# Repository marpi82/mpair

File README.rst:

======
mpair
======

Advanced Air Quality Monitoring Station
========================================

**mpair** is an open-source IoT air quality monitoring station with support for Matter/Thread protocol, PoE+ connectivity, and professional-grade sensors.

.. image:: https://img.shields.io/badge/Hardware-CERN--OHL--S--2.0-blue
   :target: LICENSE-hardware.rst
   :alt: Hardware License

.. image:: https://img.shields.io/badge/Software-GPL--3.0-green
   :target: LICENSE-software.rst
   :alt: Software License

.. image:: https://img.shields.io/badge/Documentation-CC--BY--SA--4.0-orange
   :target: LICENSE-docs.rst
   :alt: Documentation License

Features
========

Hardware Features
-----------------

* **Single MCU Architecture**

  * ESP32-C6-WROOM-1-N8 (all-in-one controller with integrated 802.15.4 radio)

* **Connectivity**

  * Matter over Thread support (native 802.15.4 radio)
  * WiFi 6 (802.11ax) 2.4GHz
  * Ethernet 10/100Mbps via W5500 (SPI)
  * PoE/PoE+ (802.3af/at) with RT5300B-12V or 12V DC jack
  * CP2102 USB-UART converter for programming

* **Sensors**

  * SPS30 - Particulate Matter sensor (PM1.0, PM2.5, PM4.0, PM10)
  * MH-Z14A - NDIR CO₂ sensor
  * SHT31 - Temperature and humidity (indoor)
  * BME280 - Temperature, humidity, and barometric pressure (outdoor)
  * GPS NEO-6 - Location and time synchronization

* **Additional Features**

  * PTC heater (70°C) for HECA - heats air to reduce relative humidity and prevent SPS30 from measuring water droplets
  * WS2812 RGB LED indicators
  * SSD1309 2.42" OLED display (128×64, optional for indoor version)

Software Features
-----------------

* Matter/Thread protocol support for smart home integration
* Real-time air quality monitoring
* Data logging and visualization
* OTA firmware updates
* Web-based configuration interface
* Multiple data export protocols:

  * MQTT broker support
  * Prometheus metrics endpoint
  * JSON REST API endpoint
  * Data publishing to Luftdaten (sensor.community)
  * Data publishing to madavi.de
  * Data publishing to opensensemap.org
  * Data publishing to aqi.eco

Technical Specifications
========================

Power Supply
------------

* **Input:** PoE/PoE+ (802.3af/at) or 12V DC jack
* **Power Rails:** 12V, 5V, 3.3V (isolated Buck converters with TX4138)
* **Consumption:** TBD

Communication Interfaces
------------------------

* **Ethernet:** 10/100Mbps via W5500 (SPI)
* **Wireless:** WiFi 6 (802.11ax) 2.4GHz, Matter over Thread (native 802.15.4 radio)
* **USB-UART:** CP2102 converter for programming and debugging

Measurement Ranges
------------------

* **PM:** 0-1000 µg/m³ (PM1.0, PM2.5, PM4.0, PM10)
* **CO₂:** 0-5000 ppm (MH-Z14A)
* **Temperature:** -40°C to +85°C
* **Humidity:** 0-100% RH
* **Pressure:** 300-1100 hPa (BME280)

Project Structure
=================

::

    mpair/
    ├── hardware/
    │   ├── EasyEDA/           # EasyEDA Pro project files
    │   ├── gerbers/           # Manufacturing files (Gerber, drill, BOM)
    │   └── schematics/        # PDF schematics and documentation
    ├── software/
    │   ├── firmware/          # ESP32 firmware (ESP-IDF / Arduino)
    │   ├── bootloader/        # Custom bootloader (if needed)
    │   └── tests/             # Unit and integration tests
    └── docs/                  # Additional documentation

Getting Started
===============

Prerequisites
-------------

* Thread Border Router (e.g., Smilight SLZB-06M) for Matter/Thread connectivity
* Smart home system with Matter support (Home Assistant, Apple Home, Google Home, etc.) - optional
* ESP-IDF v5.x or Arduino-ESP32 v3.x
* EasyEDA Pro (for hardware modifications)

Building Firmware
-----------------

.. code-block:: bash

    cd software/firmware
    idf.py build
    idf.py flash monitor

Hardware Assembly
-----------------

Detailed assembly instructions and BOM are available in the ``hardware/`` directory.

Configuration
-------------

1. Connect the device via USB, Ethernet, or power it with PoE/DC
2. Access the web interface at ``http://mpair.local``
3. Configure Thread credentials, sensor parameters, and data publishing settings
4. (Optional) Pair with your smart home system using Matter QR code
5. Configure data export endpoints (MQTT, Prometheus, Luftdaten, etc.)

Licenses
========

This project uses multiple licenses for different components:

Hardware
--------

**CERN Open Hardware Licence Version 2 - Strongly Reciprocal (CERN-OHL-S-2.0)**

The hardware designs are licensed under CERN-OHL-S-2.0, which means:

* You are free to use, modify, and distribute the hardware designs
* Any modifications must be released under the same license
* You must make design sources available
* Commercial use is allowed

See `LICENSE-hardware.rst <LICENSE-hardware.rst>`_ for full license text.

Software
--------

**GNU General Public License v3.0 (GPL-3.0)**

The software (firmware, utilities) is licensed under GPL-3.0, which means:

* You are free to use, modify, and distribute the software
* Any modifications must be released under the same license
* Source code must be made available
* Commercial use is allowed

See `LICENSE-software.rst <LICENSE-software.rst>`_ for full license text.

Documentation
-------------

**Creative Commons Attribution-ShareAlike 4.0 International (CC BY-SA 4.0)**

All documentation is licensed under CC BY-SA 4.0, which means:

* You are free to share and adapt the documentation
* You must give appropriate credit
* You must distribute your contributions under the same license
* Commercial use is allowed

See `LICENSE-docs.rst <LICENSE-docs.rst>`_ for full license text.

Contributing
============

Contributions are welcome! Please:

1. Fork the repository
2. Create a feature branch (``git checkout -b feature/amazing-feature``)
3. Commit your changes (``git commit -m 'Add amazing feature'``)
4. Push to the branch (``git push origin feature/amazing-feature``)
5. Open a Pull Request

Please ensure your contributions comply with the respective licenses.

Credits
=======

* Inspired by NAMF (Nettigo Air Monitor Firmware)
* Hardware design references from Olimex ESP32-PoE2
* Matter/Thread support via ESP-IDF

Support
=======

* **Issues:** Use GitHub Issues for bug reports and feature requests
* **Discussions:** Use GitHub Discussions for questions and ideas
* **Documentation:** Check the `docs/ <docs/>`_ directory for detailed information

Roadmap
=======

* ☐ PCB design and prototyping
* ☐ Firmware development (ESP32-C6)
* ☐ Matter device type implementation
* ☐ Home Assistant integration and testing
* ☐ Enclosure design (3D printable)
* ☐ Certification (optional - Matter, PoE)
* ☐ Production-ready version

Disclaimer
==========

This project is provided "as-is" without any warranty. The authors are not responsible for any damage or data loss resulting from the use of this hardware or software.

----

**Made with ❤️ for clean air monitoring**

*Version: 0.1.0-alpha*

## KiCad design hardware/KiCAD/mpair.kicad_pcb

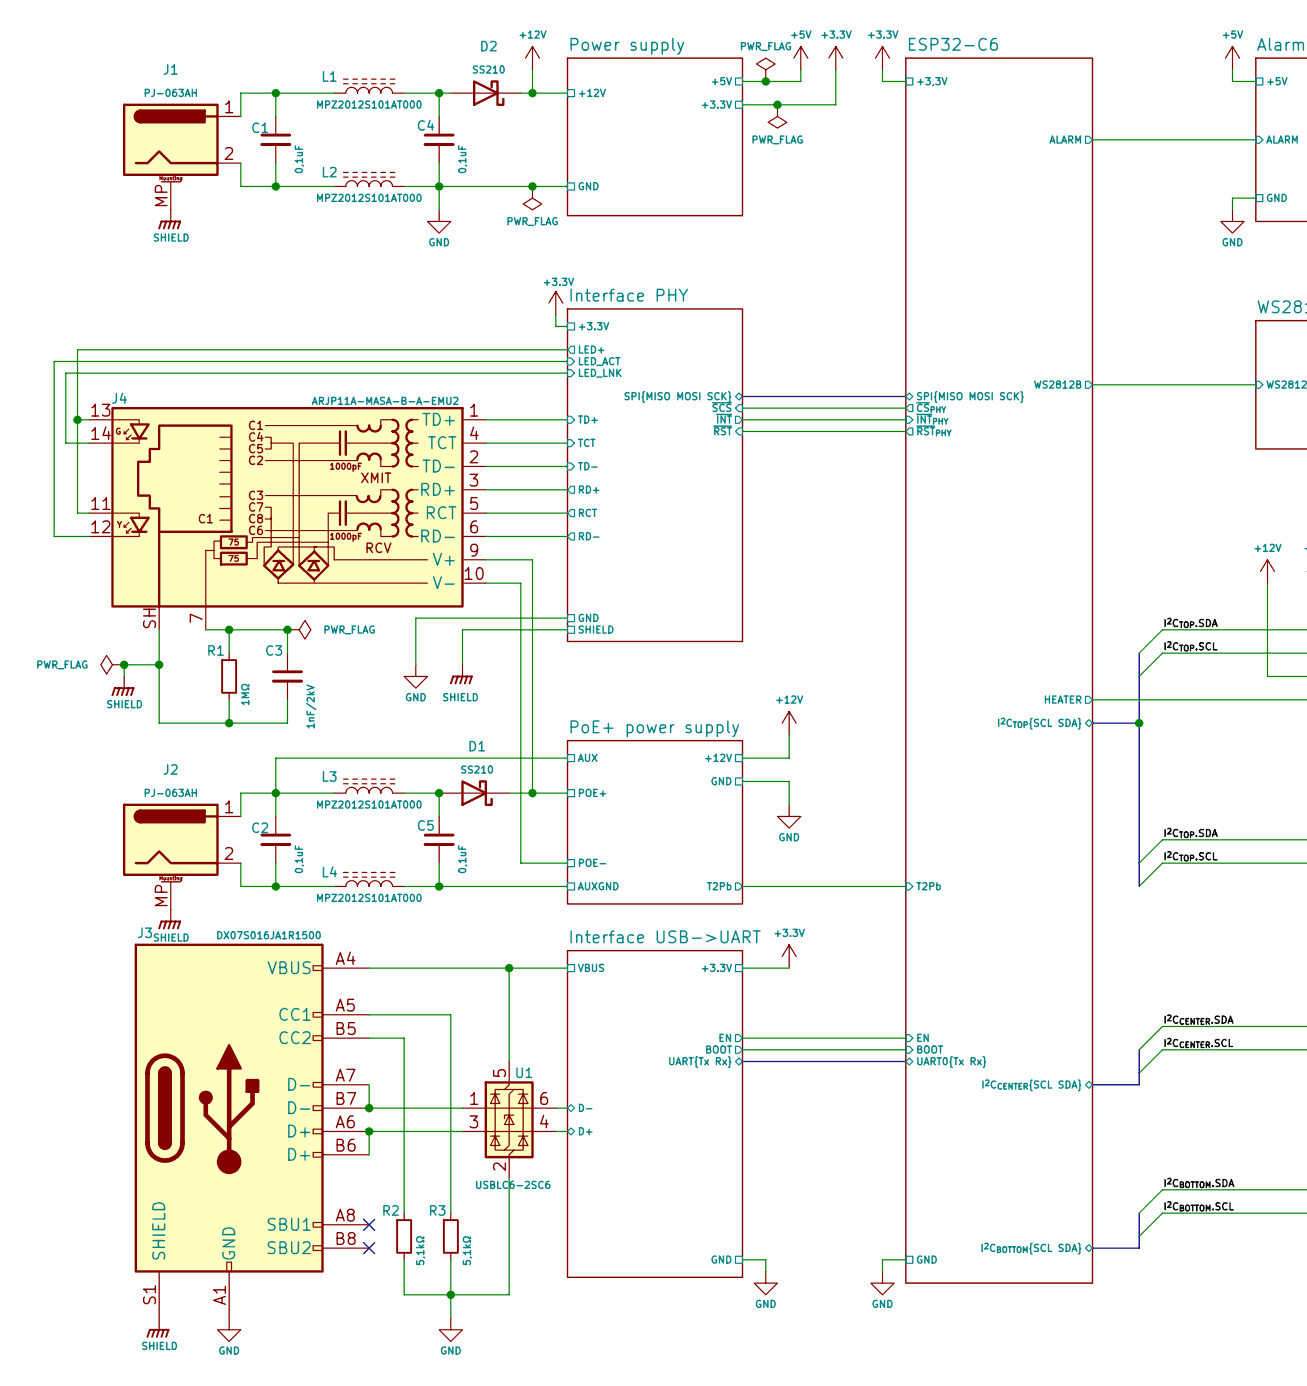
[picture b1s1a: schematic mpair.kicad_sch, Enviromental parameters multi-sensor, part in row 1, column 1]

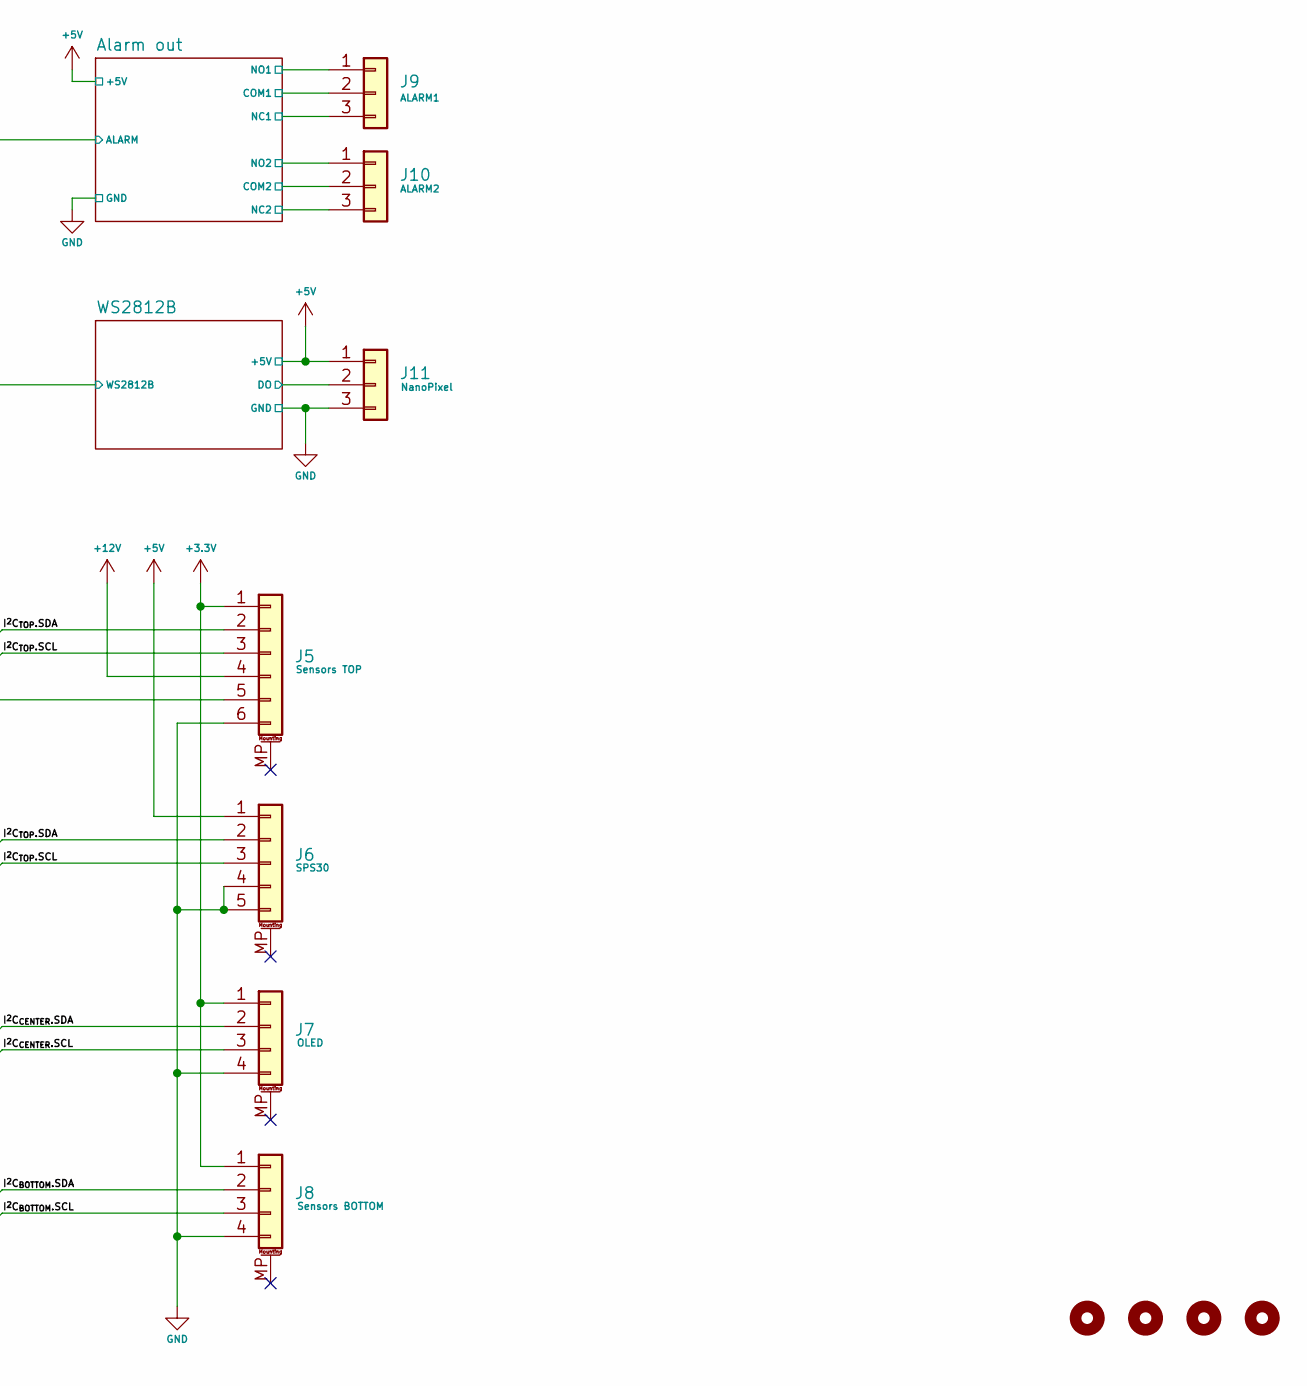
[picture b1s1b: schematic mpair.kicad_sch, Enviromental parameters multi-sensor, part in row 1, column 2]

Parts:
C1, C2, C4, C5: 0,1uF; C_0603_1608Metric; Manufacturer_Part_Number Samsung; DigiKey_Part_Number 1276-1018-1-ND
C3: 1nF/2kV; C_1812_4532Metric; Manufacturer_Part_Number Kemet; DigiKey_Part_Number 399-C1812C102KGRACTUCT-ND
D1, D2: SS210; D_SMA; Manufacturer_Part_Number Comchip Technology; DigiKey_Part_Number 641-SS210-HFCT-ND
H1, H2, H3, H4: MountingHole; MountingHole_2.7mm_M2.5
J1, J2: PJ-063AH; BarrelJack_CUI_PJ-063AH_Horizontal; Manufacturer_Part_Number Same Sky (Formerly CUI Devices); DigiKey_Part_Number CP-063AH-ND
J3: DX07S016JA1R1500; USB_C_Receptacle_JAE_DX07S016JA1R1500; Manufacturer_Part_Number JAE Electronics; DigiKey_Part_Number 670-DX07S016JA1R1500CT-ND
J4: ARJP11A-MASA-B-A-EMU2; RJ45_Abracon_ARJP11A-MA_Horizontal; Manufacturer_Part_Number Abracon LLC; DigiKey_Part_Number ARJP11A-MASA-B-A-EMU2-ND
J5: JST_ZH_B6B-ZR-SM4-TF_1x06-1MP_P1.50mm_Vertical; Manufacturer_Part_Number JST Sales America Inc.; DigiKey_Part_Number 455-B6B-ZR-SM4-TFCT-ND
J6: JST_ZH_B5B-ZR-SM4-TF_1x05-1MP_P1.50mm_Vertical; Manufacturer_Part_Number JST Sales America Inc.; DigiKey_Part_Number 455-1684-1-ND
J7, J8: JST_ZH_B4B-ZR-SM4-TF_1x04-1MP_P1.50mm_Vertical; Manufacturer_Part_Number JST Sales America Inc.; DigiKey_Part_Number 455-B4B-ZR-SM4-TFCT-ND
J9, J10, J11: Molex_KK-254_AE-6410-03A_1x03_P2.54mm_Vertical; Manufacturer_Part_Number Molex; DigiKey_Part_Number WM4112-ND
L1, L2, L3, L4: MPZ2012S101AT000; L_0805_2012Metric; Manufacturer_Part_Number TDK Corporation; DigiKey_Part_Number 445-MPZ2012S101AT000CT-ND
R1: 1MΩ; R_0603_1608Metric; Tolerance 1%; Manufacturer_Part_Number Vishay Dale; DigiKey_Part_Number 541-1.00MHCT-ND
R2, R3: 5,1kΩ; R_0603_1608Metric; Tolerance 1%; Manufacturer_Part_Number Vishay Dale; DigiKey_Part_Number 541-5.10KHCT-ND
U1: USBLC6-2SC6; SOT-23-6; Manufacturer_Part_Number Shenzhen Slkormicro Semicon Co., Ltd.; DigiKey_Part_Number 5399-USBLC6-2SC6CT-ND

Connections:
+3.3V: J5.1, J7.1, J8.1; also elsewhere on the board
+5V: J6.1, J11.1; also elsewhere on the board
+12V: D2.1 (K), J5.4; also elsewhere on the board
/Alarm out/COM1: J9.2; also elsewhere on the board
/Alarm out/COM2: J10.2; also elsewhere on the board
/Alarm out/NC1: J9.3; also elsewhere on the board
/Alarm out/NC2: J10.3; also elsewhere on the board
/Alarm out/NO1: J9.1; also elsewhere on the board
/Alarm out/NO2: J10.1; also elsewhere on the board
/ESP32-C6/HEATER: J5.5; also elsewhere on the board
/ESP32-C6/I^{2}C_{BOTTOM}.SCL: J8.3; also elsewhere on the board
/ESP32-C6/I^{2}C_{BOTTOM}.SDA: J8.2; also elsewhere on the board
/ESP32-C6/I^{2}C_{CENTER}.SCL: J7.3; also elsewhere on the board
/ESP32-C6/I^{2}C_{CENTER}.SDA: J7.2; also elsewhere on the board
/ESP32-C6/I^{2}C_{TOP}.SCL: J5.3, J6.3; also elsewhere on the board
/ESP32-C6/I^{2}C_{TOP}.SDA: J5.2, J6.2; also elsewhere on the board
/Interface PHY/LED+: J4.11, J4.13; also elsewhere on the board
/Interface PHY/LED_ACT: J4.12; also elsewhere on the board
/Interface PHY/LED_LNK: J4.14; also elsewhere on the board
/Interface PHY/RCT: J4.5 (RCT); also elsewhere on the board
/Interface PHY/RD+: J4.3 (RD+); also elsewhere on the board
/Interface PHY/RD-: J4.6 (RD-); also elsewhere on the board
/Interface PHY/TCT: J4.4 (TCT); also elsewhere on the board
/Interface PHY/TD+: J4.1 (TD+); also elsewhere on the board
/Interface PHY/TD-: J4.2 (TD-); also elsewhere on the board
/Interface USB->UART/D+: U1.4 (I/O2); also elsewhere on the board
/Interface USB->UART/D-: U1.6 (I/O1); also elsewhere on the board
/Interface USB->UART/VBUS: J3.A4 (VBUS), J3.A9 (VBUS), J3.B4 (VBUS), J3.B9 (VBUS), U1.5 (VBUS); also elsewhere on the board
/PoE+ power supply/AUX: C2.1, J2.1, L3.1; also elsewhere on the board
/PoE+ power supply/AUXGND: C5.2, J4.10 (V-), L4.2; also elsewhere on the board
/PoE+ power supply/POE+: D1.1 (K), J4.9 (V+); also elsewhere on the board
/WS2812B/DO: J11.2; also elsewhere on the board
GND: C4.2, J3.A1 (GND), J3.A12 (GND), J3.B1 (GND), J3.B12 (GND), J5.6, J6.4, J6.5, J7.4, J8.4, J11.3, L2.2, R2.2, R3.2, U1.2 (GND); also elsewhere on the board
unnamed: C1.1, J1.1, L1.1
unnamed: C1.2, J1.2, L2.1
unnamed: C2.2, J2.2, L4.1
unnamed: C3.1, J4.7, R1.1
unnamed: C5.1, D1.2 (A), L3.2
unnamed: C4.1, D2.2 (A), L1.2
unnamed: J3.A5 (CC1), R3.1
unnamed: J3.B5 (CC2), R2.1
unnamed: J3.A6 (D+), J3.B6 (D+), U1.3 (I/O2)
unnamed: J3.A7 (D-), J3.B7 (D-), U1.1 (I/O1)
SHIELD: C3.2, J1.MP (MountPin), J2.MP (MountPin), J3.S1 (SHIELD), J4.SH, R1.2; also elsewhere on the board

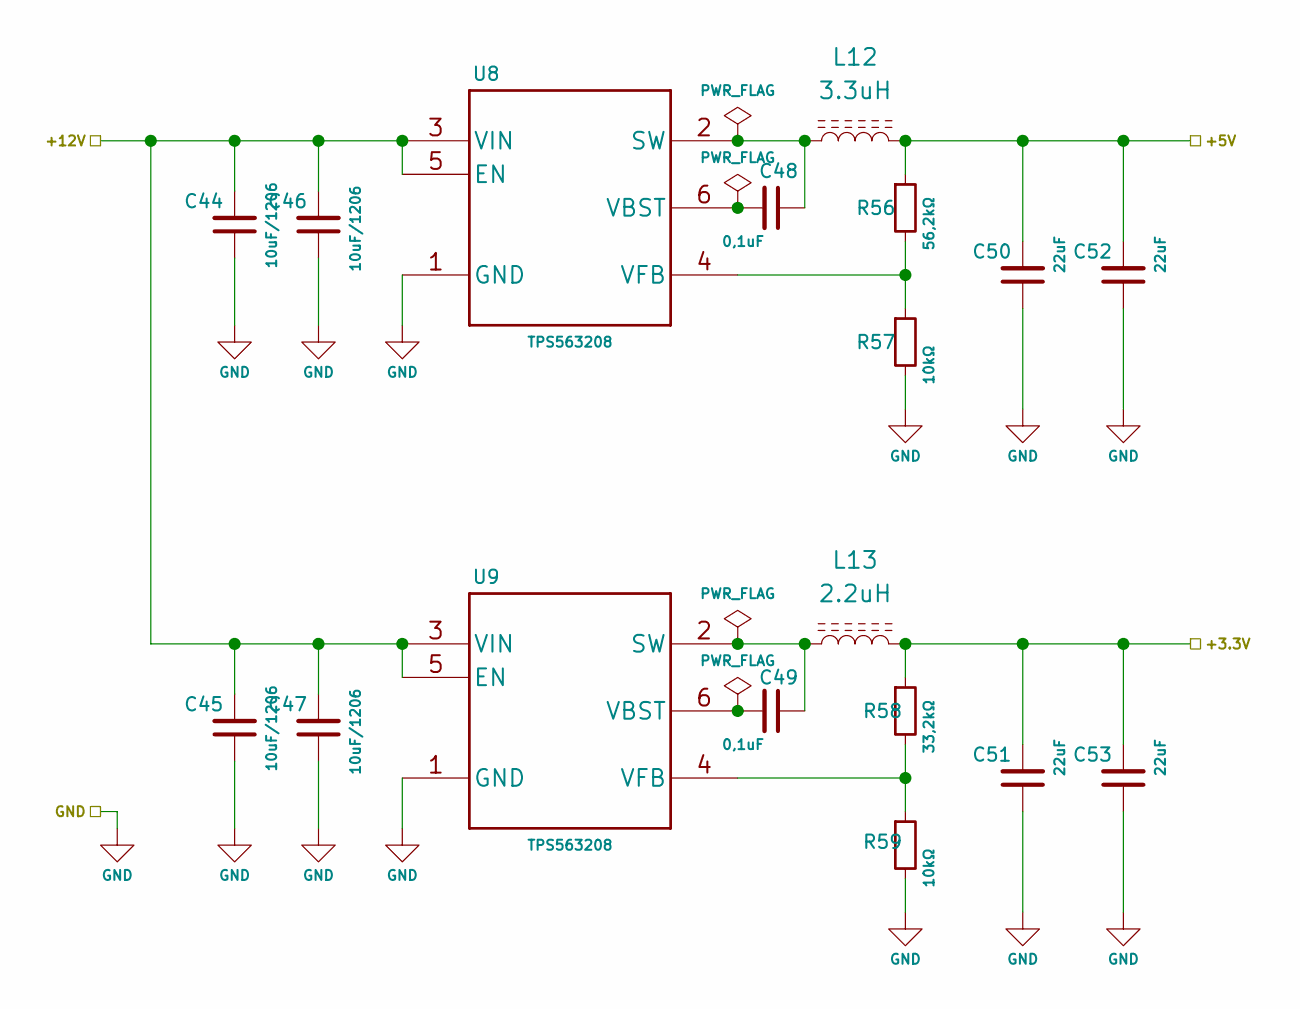
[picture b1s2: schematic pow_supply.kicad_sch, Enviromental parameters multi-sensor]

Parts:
C44, C45, C46, C47: 10uF/1206; C_1210_3225Metric; Manufacturer_Part_Number TDK; DigiKey_Part_Number 445-3942-1-ND
C48, C49: 0,1uF; C_0603_1608Metric; Manufacturer_Part_Number Samsung; DigiKey_Part_Number 1276-1018-1-ND
C50, C51, C52, C53: 22uF; C_1210_3225Metric; Manufacturer_Part_Number Samsung; DigiKey_Part_Number 1276-3392-1-ND
L12: 3.3uH; DR74; Manufacturer_Part_Number Eaton - Electronics Division; DigiKey_Part_Number 513-1665-1-ND
L13: 2.2uH; DR74; Manufacturer_Part_Number Eaton - Electronics Division; DigiKey_Part_Number 513-1140-1-ND
R56: 56,2kΩ; R_0603_1608Metric; Tolerance 1%; Manufacturer_Part_Number Vishay Dale; DigiKey_Part_Number 541-56.2KHCT-ND
R57, R59: 10kΩ; R_0603_1608Metric; Tolerance 1%; Manufacturer_Part_Number Vishay Dale; DigiKey_Part_Number 541-10.0KHCT-ND
R58: 33,2kΩ; R_0603_1608Metric; Tolerance 1%; Manufacturer_Part_Number Vishay Dale; DigiKey_Part_Number 541-33.2KHCT-ND
U8, U9: TPS563208; SOT-23-6; Manufacturer_Part_Number Texas Instruments; DigiKey_Part_Number 296-44844-1-ND

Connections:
+3.3V: C51.2, C53.2, L13.2, R58.1; also elsewhere on the board
+5V: C50.2, C52.2, L12.2, R56.1; also elsewhere on the board
+12V: C44.2, C45.2, C46.2, C47.2, U8.3 (VIN), U8.5 (EN), U9.3 (VIN), U9.5 (EN); also elsewhere on the board
GND: C44.1, C45.1, C46.1, C47.1, C50.1, C51.1, C52.1, C53.1, R57.2, R59.2, U8.1 (GND), U9.1 (GND); also elsewhere on the board
unnamed: C48.1, L12.1, U8.2 (SW)
unnamed: C48.2, U8.6 (VBST)
unnamed: R56.2, R57.1, U8.4 (VFB)
unnamed: C49.1, L13.1, U9.2 (SW)
unnamed: C49.2, U9.6 (VBST)
unnamed: R58.2, R59.1, U9.4 (VFB)

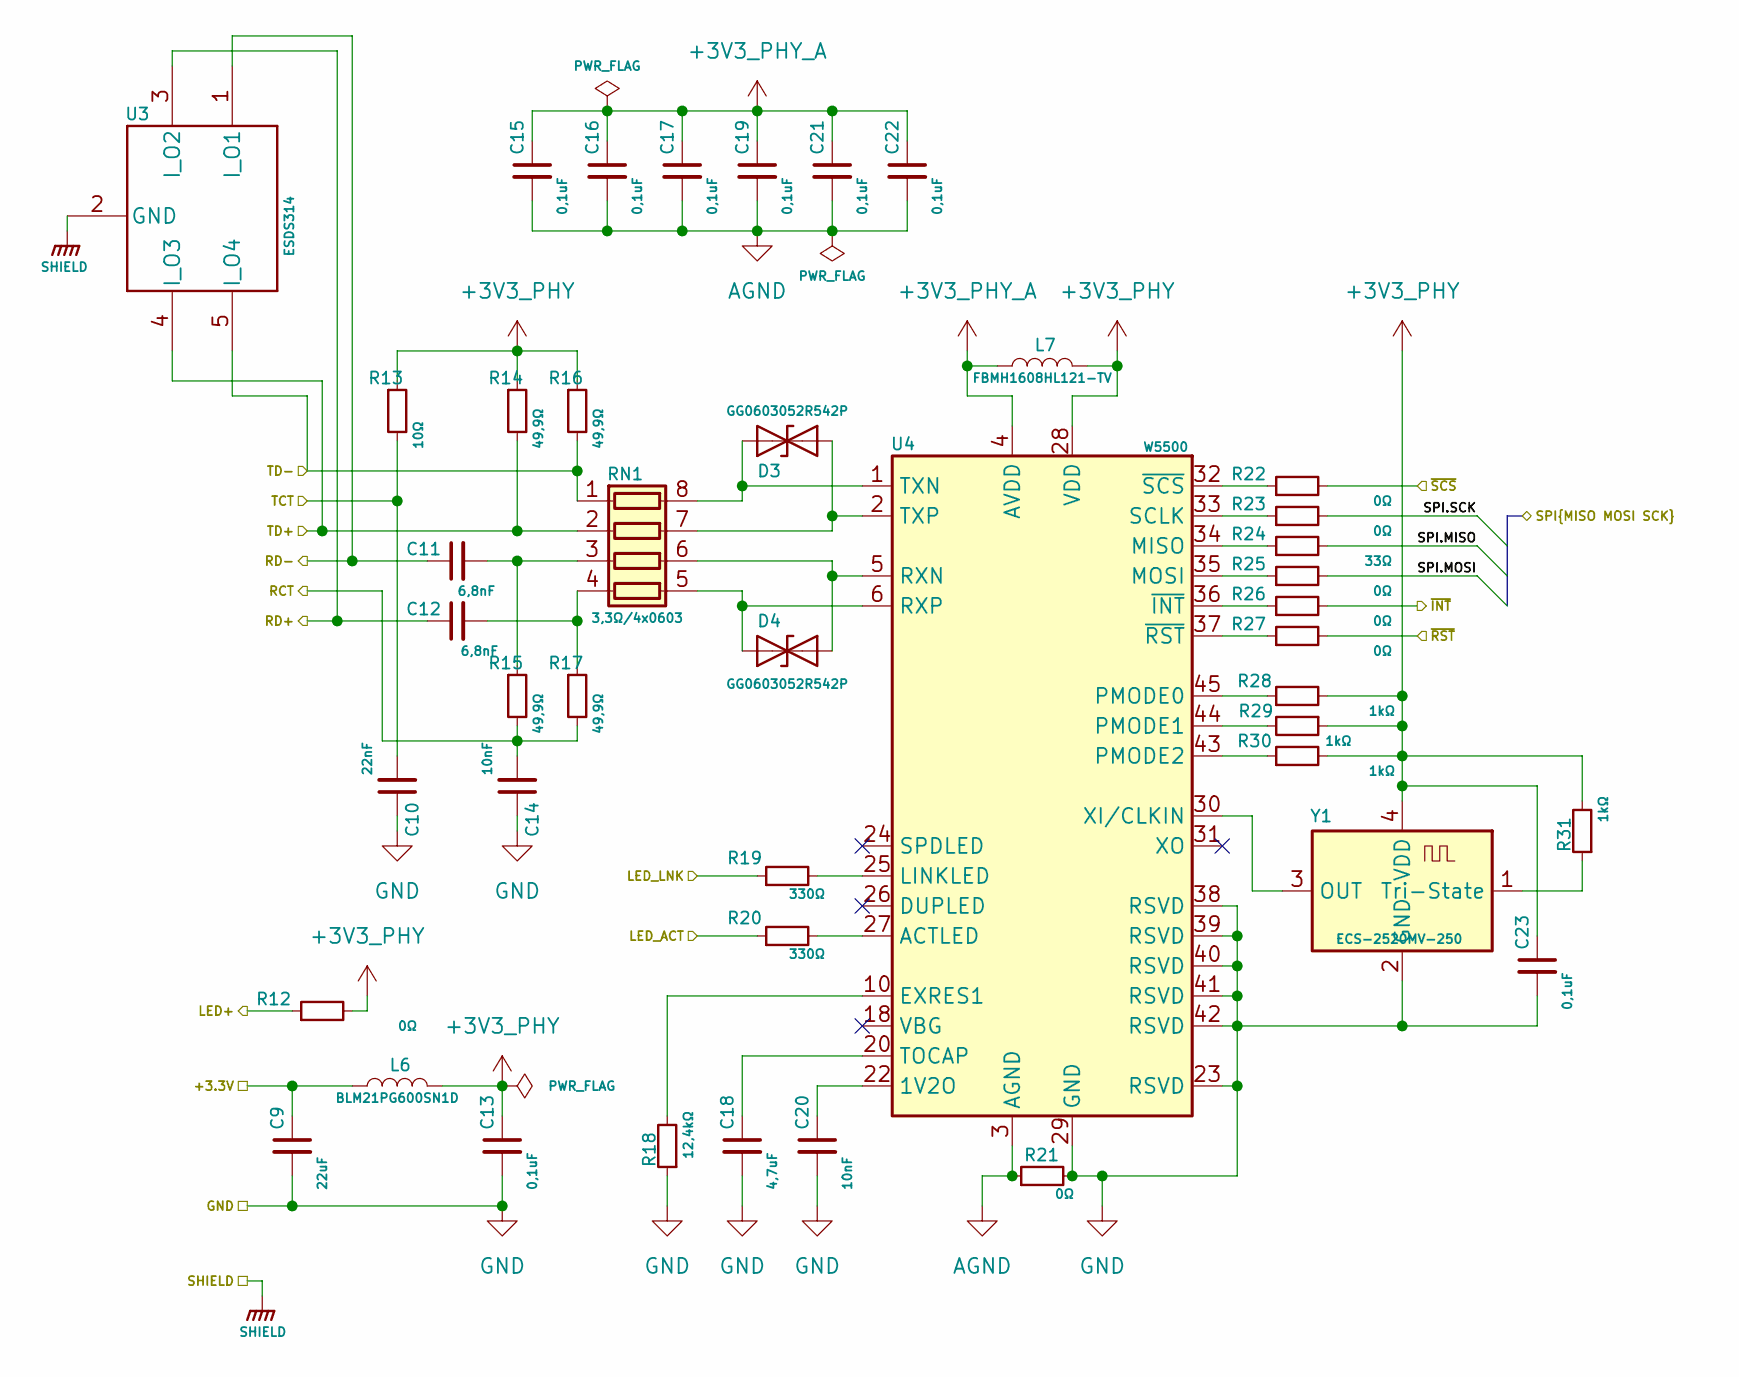
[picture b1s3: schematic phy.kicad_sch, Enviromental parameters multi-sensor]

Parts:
C9: 22uF; C_1210_3225Metric; Manufacturer_Part_Number Samsung; DigiKey_Part_Number 1276-3392-1-ND
C10: 22nF; C_0603_1608Metric; Manufacturer_Part_Number Murata; DigiKey_Part_Number 490-4782-1-ND
C11, C12: 6,8nF; C_0603_1608Metric; Manufacturer_Part_Number Kyocera; DigiKey_Part_Number 478-KAM15AR72A682KTCT-ND
C13, C15, C16, C17, C19, C21, C22, C23: 0,1uF; C_0603_1608Metric; Manufacturer_Part_Number Samsung; DigiKey_Part_Number 1276-1018-1-ND
C14, C20: 10nF; C_0603_1608Metric; Manufacturer_Part_Number Samsung; DigiKey_Part_Number 1276-1009-1-ND
C18: 4,7uF; C_0805_2012Metric; Manufacturer_Part_Number Samsung; DigiKey_Part_Number 1276-2970-1-ND
D3, D4: GG0603052R542P; D_0603_1608Metric; Manufacturer_Part_Number Kyocera; DigiKey_Part_Number 478-GG0603052R542PCT-ND
L6: BLM21PG600SN1D; L_0805_2012Metric; Manufacturer_Part_Number Murata Electronics; DigiKey_Part_Number 490-1053-1-ND
L7: FBMH1608HL121-TV; L_0603_1608Metric; Manufacturer_Part_Number Taiyo Yuden; DigiKey_Part_Number 587-3812-1-ND
R12, R21, R22, R23, R25, R26, R27: 0Ω; R_0603_1608Metric; Tolerance 1%; Manufacturer_Part_Number Vishay Dale; DigiKey_Part_Number 541-0.0GCT-ND
R13: 10Ω; R_0603_1608Metric; Tolerance 1%; Manufacturer_Part_Number Vishay Dale; DigiKey_Part_Number 541-10.0HCT-ND
R14, R15, R16, R17: 49,9Ω; R_0603_1608Metric; Tolerance 1%; Manufacturer_Part_Number Vishay Dale; DigiKey_Part_Number 541-49.9HCT-ND
R18: 12,4kΩ; R_0603_1608Metric; Tolerance 1%; Manufacturer_Part_Number Vishay Dale; DigiKey_Part_Number 541-12.4KHCT-ND
R19, R20: 330Ω; R_0603_1608Metric; Tolerance 1%; Manufacturer_Part_Number Vishay Dale; DigiKey_Part_Number 541-330HCT-ND
R24: 33Ω; R_0603_1608Metric; Tolerance 1%; Manufacturer_Part_Number Vishay Dale; DigiKey_Part_Number 541-33.0HCT-ND
R28, R29, R30, R31: 1kΩ; R_0603_1608Metric; Tolerance 1%; Manufacturer_Part_Number Vishay Dale; DigiKey_Part_Number 541-1.00KHCT-ND
RN1: 3,3Ω/4x0603; R_Array_Concave_4x0603; Tolerance 5%; Manufacturer_Part_Number Panasonic Electronic Components; DigiKey_Part_Number Y43R3CT-ND
U3: ESDS314; SOT-23-5; Manufacturer_Part_Number Texas Instruments; DigiKey_Part_Number 296-ESDS314DBVRCT-ND
U4: W5500; LQFP-48_7x7mm_P0.5mm; Manufacturer_Part_Number WIZnet; DigiKey_Part_Number 1278-W5500CT-ND
Y1: ECS-2520MV-250; Oscillator_SMD_ECS_2520MV-xxx-xx-4Pin_2.5x2.0mm; Manufacturer_Part_Number ECS Inc.; DigiKey_Part_Number XC2752CT-ND

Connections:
+3.3V: C9.1, L6.1; also elsewhere on the board
+3V3_PHY: C13.1, C23.1, L6.2, L7.2, R12.2, R13.1, R14.1, R16.1, R28.2, R29.1, R30.2, R31.2, U4.28 (VDD), Y1.4 (VDD)
+3V3_PHY_A: C15.1, C16.1, C17.1, C19.1, C21.1, C22.1, L7.1, U4.4 (AVDD), U4.8 (AVDD), U4.11 (AVDD), U4.15 (AVDD), U4.17 (AVDD), U4.21 (AVDD)
/ESP32-C6/SPI.MISO: R24.2; also elsewhere on the board
/ESP32-C6/SPI.MOSI: R25.2; also elsewhere on the board
/ESP32-C6/SPI.SCK: R23.2; also elsewhere on the board
/ESP32-C6/~CS_{PHY}: R22.2; also elsewhere on the board
/ESP32-C6/~INT_{PHY}: R26.2; also elsewhere on the board
/ESP32-C6/~RST_{PHY}: R27.2; also elsewhere on the board
/Interface PHY/LED+: R12.1; also elsewhere on the board
/Interface PHY/LED_ACT: R20.1; also elsewhere on the board
/Interface PHY/LED_LNK: R19.1; also elsewhere on the board
/Interface PHY/RCT: C14.2, R15.2, R17.2; also elsewhere on the board
/Interface PHY/RD+: C12.1, U3.3 (I_O2); also elsewhere on the board
/Interface PHY/RD-: C11.1, U3.1 (I_O1); also elsewhere on the board
/Interface PHY/TCT: C10.2, R13.2; also elsewhere on the board
/Interface PHY/TD+: R14.2, RN1.2 (R2.1), U3.4 (I_O3); also elsewhere on the board
/Interface PHY/TD-: R16.2, RN1.1 (R1.1), U3.5 (I_O4); also elsewhere on the board
AGND: C15.2, C16.2, C17.2, C19.2, C21.2, C22.2, R21.1, U4.3 (AGND), U4.9 (AGND), U4.14 (AGND), U4.16 (AGND), U4.19 (AGND), U4.48 (AGND)
GND: C9.2, C10.1, C13.2, C14.1, C18.2, C20.2, C23.2, R18.1, R21.2, U4.23 (RSVD), U4.29 (GND), U4.38 (RSVD), U4.39 (RSVD), U4.40 (RSVD), U4.41 (RSVD), U4.42 (RSVD), Y1.2 (GND); also elsewhere on the board
unnamed: D3.1 (A1), RN1.8 (R1.2), U4.1 (TXN)
unnamed: D3.2 (A2), RN1.7 (R2.2), U4.2 (TXP)
unnamed: D4.1 (A1), RN1.5 (R4.2), U4.6 (RXP)
unnamed: D4.2 (A2), RN1.6 (R3.2), U4.5 (RXN)
unnamed: C11.2, R15.1, RN1.3 (R3.1)
unnamed: C12.2, R17.1, RN1.4 (R4.1)
unnamed: C20.1, U4.22 (1V2O)
unnamed: R20.2, U4.27 (ACTLED)
unnamed: R18.2, U4.10 (EXRES1)
unnamed: R19.2, U4.25 (LINKLED)
unnamed: R24.1, U4.34 (MISO)
unnamed: R25.1, U4.35 (MOSI)
unnamed: R28.1, U4.45 (PMODE0)
unnamed: R29.2, U4.44 (PMODE1)
unnamed: R30.1, U4.43 (PMODE2)
unnamed: R23.1, U4.33 (SCLK)
unnamed: C18.1, U4.20 (TOCAP)
unnamed: U4.30 (XI/CLKIN), Y1.3 (OUT)
unnamed: R26.1, U4.36 (~INT)
unnamed: R27.1, U4.37 (~RST)
unnamed: R22.1, U4.32 (~SCS)
unnamed: R31.1, Y1.1 (Tri-State)
SHIELD: U3.2 (GND); also elsewhere on the board

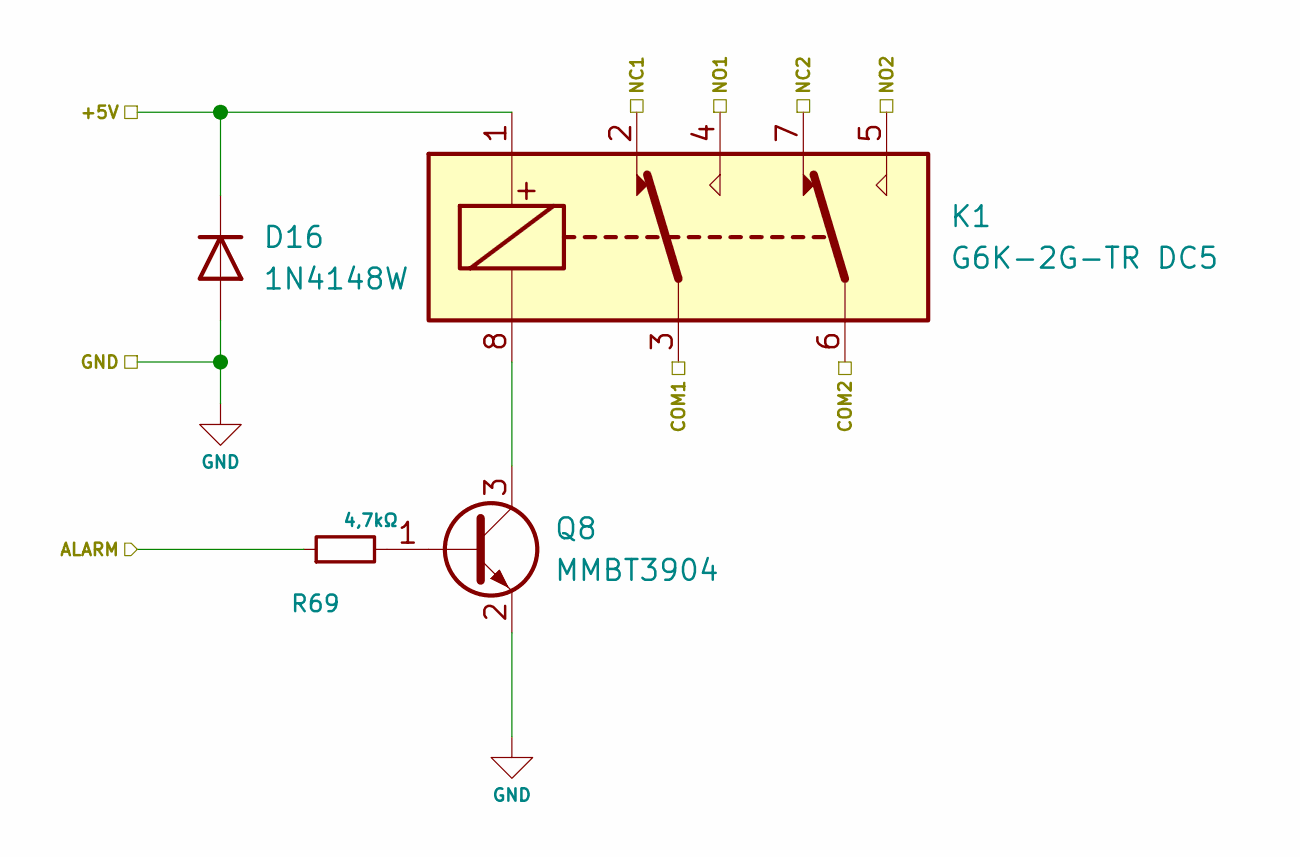
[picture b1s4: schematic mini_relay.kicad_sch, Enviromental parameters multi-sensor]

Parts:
D16: 1N4148W; D_SOD-123; Manufacturer_Part_Number Diodes Incorporated; DigiKey_Part_Number 31-1N4148W-7-F-WCT-ND
K1: G6K-2G-TR DC5; Relay_DPDT_Omron_G6K-2G; Manufacturer_Part_Number Omron Electronics Inc-EMC Div; DigiKey_Part_Number Z2657CT-ND
Q8: MMBT3904; SC-59; Manufacturer_Part_Number Taiwan Semiconductor Corporation; DigiKey_Part_Number 1801-MMBT3904HRFGCT-ND
R69: 4,7kΩ; R_0603_1608Metric; Tolerance 1%; Manufacturer_Part_Number Vishay Dale; DigiKey_Part_Number 541-4.70KHCT-ND

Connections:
+5V: D16.1 (K), K1.1; also elsewhere on the board
/Alarm out/COM1: K1.3; also elsewhere on the board
/Alarm out/COM2: K1.6; also elsewhere on the board
/Alarm out/NC1: K1.2; also elsewhere on the board
/Alarm out/NC2: K1.7; also elsewhere on the board
/Alarm out/NO1: K1.4; also elsewhere on the board
/Alarm out/NO2: K1.5; also elsewhere on the board
/ESP32-C6/ALARM: R69.1; also elsewhere on the board
GND: D16.2 (A), Q8.2 (E); also elsewhere on the board
unnamed: Q8.1 (B), R69.2
unnamed: K1.8, Q8.3 (C)

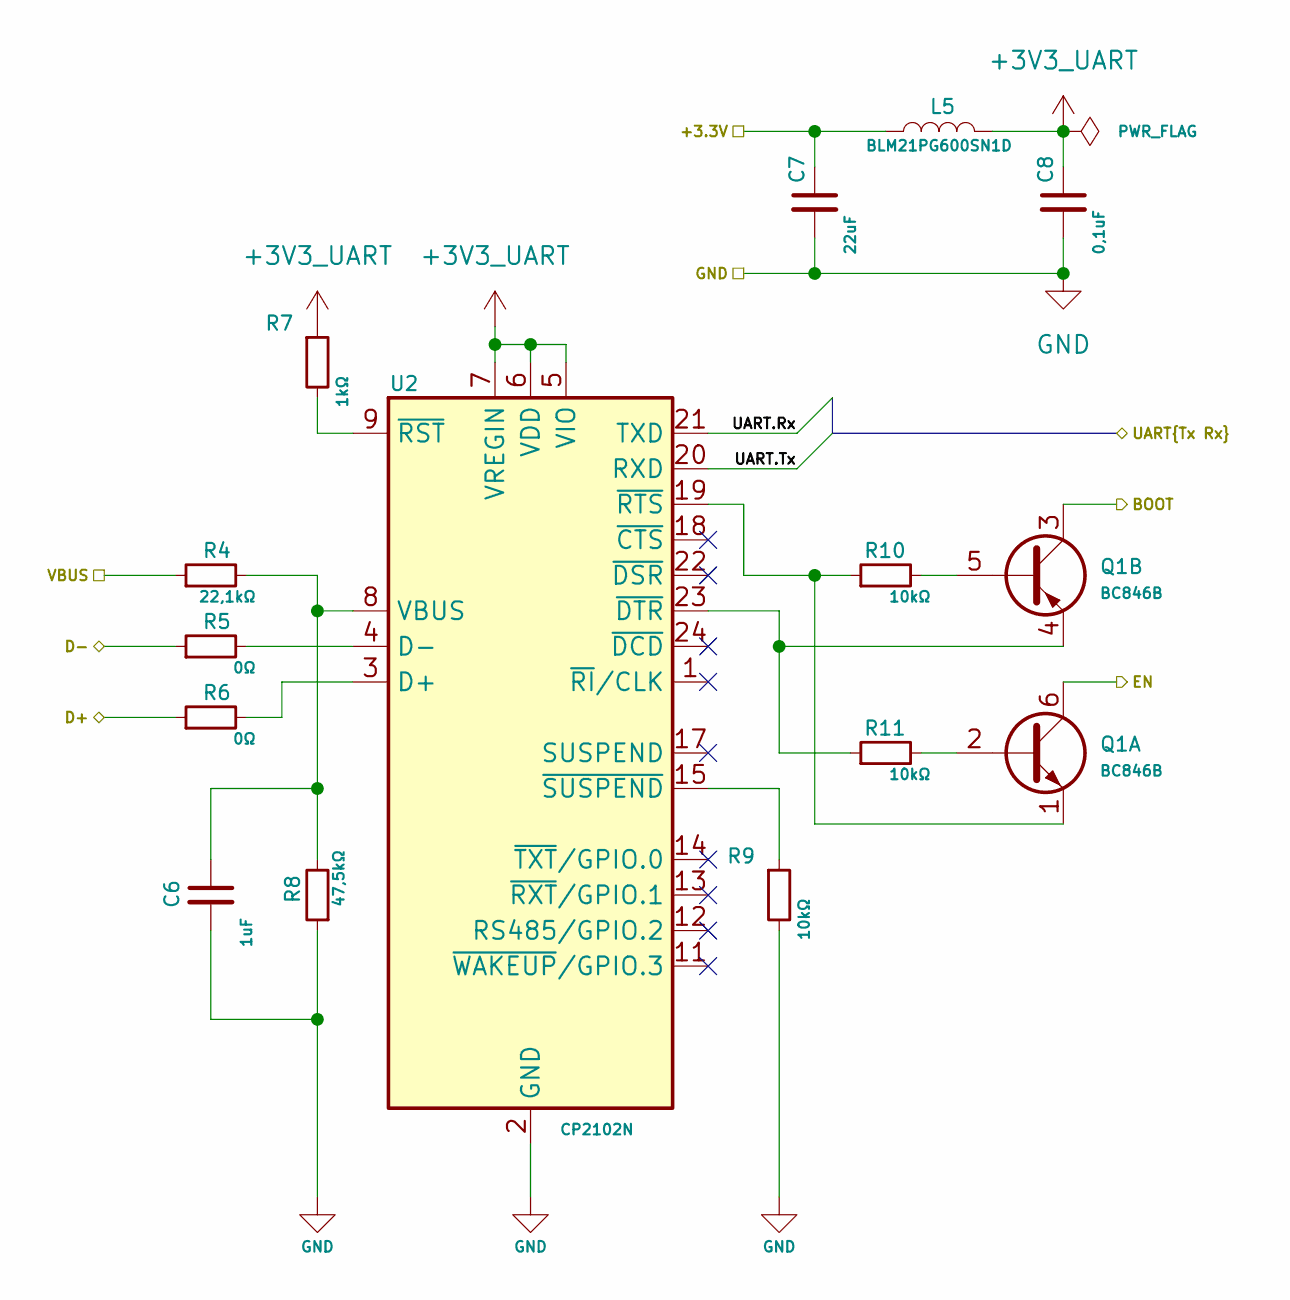
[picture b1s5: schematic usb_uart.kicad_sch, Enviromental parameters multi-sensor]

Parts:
C6: 1uF; C_0805_2012Metric; Manufacturer_Part_Number Samsung; DigiKey_Part_Number 1276-1066-1-ND
C7: 22uF; C_1210_3225Metric; Manufacturer_Part_Number Samsung; DigiKey_Part_Number 1276-3392-1-ND
C8: 0,1uF; C_0603_1608Metric; Manufacturer_Part_Number Samsung; DigiKey_Part_Number 1276-1018-1-ND
L5: BLM21PG600SN1D; L_0805_2012Metric; Manufacturer_Part_Number Murata Electronics; DigiKey_Part_Number 490-1053-1-ND
Q1: BC846B; SOT-363_SC-70-6; Manufacturer_Part_Number Nexperia USA Inc.; DigiKey_Part_Number 1727-4846-1-ND
R4: 22,1kΩ; R_0603_1608Metric; Tolerance 1%; Manufacturer_Part_Number Vishay Dale; DigiKey_Part_Number 541-22.1KHCT-ND
R5, R6: 0Ω; R_0603_1608Metric; Tolerance 1%; Manufacturer_Part_Number Vishay Dale; DigiKey_Part_Number 541-0.0GCT-ND
R7: 1kΩ; R_0603_1608Metric; Tolerance 1%; Manufacturer_Part_Number Vishay Dale; DigiKey_Part_Number 541-1.00KHCT-ND
R8: 47,5kΩ; R_0603_1608Metric; Tolerance 1%; Manufacturer_Part_Number Vishay Dale; DigiKey_Part_Number 541-47.5KHCT-ND
R9, R10, R11: 10kΩ; R_0603_1608Metric; Tolerance 1%; Manufacturer_Part_Number Vishay Dale; DigiKey_Part_Number 541-10.0KHCT-ND
U2: CP2102N; QFN-24-1EP_4x4mm_P0.5mm_EP2.6x2.6mm; Manufacturer_Part_Number Silicon Labs; DigiKey_Part_Number 336-5888-1-ND

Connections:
+3.3V: C7.1, L5.1; also elsewhere on the board
+3V3_UART: C8.1, L5.2, R7.1, U2.5 (VIO), U2.6 (VDD), U2.7 (VREGIN)
/ESP32-C6/BOOT: Q1.3 (C2); also elsewhere on the board
/ESP32-C6/EN: Q1.6 (C1); also elsewhere on the board
/ESP32-C6/UART0.Rx: U2.21 (TXD); also elsewhere on the board
/ESP32-C6/UART0.Tx: U2.20 (RXD); also elsewhere on the board
/Interface USB->UART/D+: R6.1; also elsewhere on the board
/Interface USB->UART/D-: R5.1; also elsewhere on the board
/Interface USB->UART/VBUS: R4.1; also elsewhere on the board
GND: C6.2, C7.2, C8.2, R8.1, R9.2, U2.2 (GND), U2.25 (GND); also elsewhere on the board
unnamed: Q1.2 (B1), R11.2
unnamed: Q1.1 (E1), R10.1, U2.19 (~RTS)
unnamed: Q1.5 (B2), R10.2
unnamed: Q1.4 (E2), R11.1, U2.23 (~DTR)
unnamed: R6.2, U2.3 (D+)
unnamed: R5.2, U2.4 (D-)
unnamed: C6.1, R4.2, R8.2, U2.8 (VBUS)
unnamed: R7.2, U2.9 (~RST)
unnamed: R9.1, U2.15 (~SUSPEND)
